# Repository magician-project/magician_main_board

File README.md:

# Magician Main Board for Sensing Robot

This project implements a **multi-laser distance sensing and light control system** on an **Arduino Nano (ATmega328P)**. 

> This README documents the original [`src/kicad/v1`](src/kicad/v1/README.md) board and its Arduino Nano firmware. The current hardware revision is **MagicianCam4** ([`src/kicad/v4`](src/kicad/v4/README.md)), built around a Raspberry Pi Pico 2 with a VL53L5CX multizone ToF sensor; its firmware lives in [`src/pico2`](src/pico2/).

The software that drives this PCB (along with the Camera/ATI/Teensy) is the [Magician Grabber](https://github.com/magician-project/magician_grabber)

It integrates:

- **3x VL53L0X time-of-flight distance sensors** (over I²C, with unique addresses via XSHUT control) 
- **Up to 8 lights** controlled via direct GPIO or a **74HC595 shift register**
- **Extendable up to 64 lights** by daisy chaining more **74HC595 shift registers**
- **Ethernet W5100 support** (Telnet-style interface) 
- **Two analog input buttons** for manual interaction
- **Serial + Ethernet reporting** of sensor readings, light state, and button presses

The firmware cycles lights automatically, can react to distance sensor readings, and supports both **serial commands** and **Ethernet control**.

---

## Features

- 🔦 **3x VL53L0X** laser distance sensors on a shared I²C bus
- 💡 **6x-8x LED light outputs** (6x direct pin mode or 8x via 74HC595 shift register)
- 🌐 **Ethernet W5100 support** with telnet-style server on port `23`
- 🎛️ **Two analog buttons** (for annotations / input)
- ⚡ **Low-level SRAM monitoring** and reset recovery functions
- 🛠️ **Configurable light modes:**
  - Sequential cycling
  - Pulse mode
  - Sensor-based closest-light decision
  - Timed flashing

---

## Setup

Important: Before connecting the board, [read the following guide](doc/connectors.md)!

## Hardware Components

- **Arduino Nano with USB-Micro port/ UNO (ATmega328P)**  
- **VL53L0X distance sensors** (x3)  
- **W5100 Ethernet module/shield**  
- **74HC595 shift register** (optional, for light control)  
- **6 LEDs or lights** (controlled by direct pins or shift register)  
- **2 push buttons** (wired to analog inputs `A6` and `A7`)  

### Pin Mapping

| Component                  | Pin(s) Used         | Notes |
|-----------------------------|---------------------|-------|
| I²C (VL53L0X)              | A4 (SDA), A5 (SCL) | Shared bus |
| VL53L0X XSHUT (x3)         | A0, A1, A2         | Controls sensor reset & addressing |
| Ethernet Reset             | D9                 | Shared with `I2C_EXTRA_PIN` |
| Direct Light Outputs       | D3, D4, D5, D6, D7, D8 | Default pin mode |
| 74HC595 Latch (STCP)       | D3                 | Used if shift register enabled |
| 74HC595 Clock (SHCP)       | D4                 | 〃 |
| 74HC595 Data (DS)          | D5                 | 〃 |
| 74HC595 OE (Enable)        | D2                 | Active low |
| 74HC595 SRCLR (Clear)      | A3                 | Active low |
| Buttons                    | A6, A7             | Analog threshold detection |

---

## Software Setup

1. **Clone this repository** and the Pololu VL53L0X Arduino library:
   ```bash
   git clone https://github.com/YOUR_GITHUB_USERNAME/arduino-nano-vl53l0x-ethernet
   cd arduino-nano-vl53l0x-ethernet
   git clone https://github.com/pololu/vl53l0x-arduino
   cp vl53l0x-arduino/VL53L0X.cpp ./
   cp vl53l0x-arduino/VL53L0X.h ./

    Fix Arduino Nano memory constraints (important!):
    The VL53L0X library is heavy and may cause stack overflow resets.
    To prevent this, reduce the serial buffer sizes:

    Edit:

~/.arduino15/packages/arduino/hardware/avr/1.8.6/cores/arduino/HardwareSerial.h

Change:

    #define SERIAL_TX_BUFFER_SIZE 16
    #define SERIAL_RX_BUFFER_SIZE 8

    With this, the sketch fits:

        Program storage: ~66% used

        Dynamic memory: ~80% used (401 bytes free)

    Install dependencies in Arduino IDE:

        Wire.h (I²C, built-in)

        SPI.h (Ethernet, built-in)

        Ethernet.h (W5100)

    Upload the sketch to your Arduino Nano.

Serial & Ethernet Commands

To connect to Ethernet (assuming you are on the correct subnet)
```
telnet 192.168.137.64
```

To connect using USB/Serial (assuming you are connected over USB)
```
sudo apt install picocom
picocom -b 115200 /dev/ttyUSB0  --imap lfcrlf 
Ctrl + A + Q to exit
```

When connected via USB serial or Ethernet Telnet (port 23), you can control and query the system by supplying the following command bytes.

Command	Description:

| Command                     | Dangerous           | Description |
|-----------------------------|---------------------|-------|
| v              | No    | Print firmware version |
| h              | Yes   | Enable 74HC595 mode + auto light cycling |
| i              | Yes   | Disable 74HC595 (direct pin mode) |
| o              | Maybe | Continuous lights (disable pulsing) |
| p              | Maybe | Switch to pulsing of 500μs / Subsequent calls increase pulse length by 500µs |
| r              | No    | Reset light cycling |
| a              | No    | Enable sensor-based light selection |
| t              | No    | Enable custom cycling mode (mode 3) |
| y              | No    | Flash lights for 10s, then turn off |
| z              | No    | Turn off all lights and reset Arduino |
| 0-6            | Yes   | Manually activate light with number #N |
| +              | Yes   | Step to next light |
| f              | No    | Disable serial/Ethernet reporting |
| x              | No    | (Ethernet only) Print local IP + hardware status | 
| b              | No    | Make Analog Buttons have binary output  1/0 | 
| n              | No    | Make Analog Buttons have non-binary output  0-1024 | 

Commands marked as potentially dangerous directly alter light states that can be dangerous when
using a connected Camera Board that over volts lights. Please see [the setup guide](doc/connectors.md) to understand why. 

Data Reporting

When enabled, the Arduino periodically outputs status lines in CSV format:

<time_ms>,<button1>,<button2>,<distance1>,<distance2>,<distance3>,<light1>,<light2>,...<light6>

Example:

1050,0,1,523,812,1500,1,0,0,0,0,0

    time_ms – system uptime in ms

    button1/button2 – 0 or 1

    distanceN – measured distance in mm (F = failed, H = too high, 0 = inactive)

    lightN – 1 if active, 0 otherwise

Memory & Stability Notes

    Free SRAM is checked at startup; if less than 231 bytes are available, instability is expected.

    Use the reduced VL53L0X library and shrunk serial buffers for stability.

    A resetFunc() software reset is available to recover from low memory conditions.

Versioning

    Version: 0.26

    Major/minor defined in VERSION_MAJOR, VERSION_MINOR.

License

MIT License.
This project uses Pololu’s VL53L0X Arduino Library

Possible Future Improvements

    Add MQTT over Ethernet for IoT integration

    Support ESP32 (more SRAM, WiFi support, no buffer hacks needed)

    Add dynamic light patterns and user-configurable modes

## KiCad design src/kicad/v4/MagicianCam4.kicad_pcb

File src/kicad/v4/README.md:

Designed by Giulio Vivo

# MagicianCam4

Current revision of the Magician camera/sensing board, built around a **Raspberry Pi Pico 2 (RP2350)** instead of the Arduino Nano used in [`v1/`](../v1/README.md). Firmware lives in [`src/pico2/`](../../pico2/).

Main changes over v1:

- **VL53L5CX multizone ToF sensor** (8x8 = 64 distance zones) replacing the 3x VL53L0X single-zone sensors.
- **MCP23018 I²C I/O expander** for buttons and light control, replacing the 74HC595 shift register chain.
- Exposure-synced LED strobing with per-COB thermal budgeting, since the LED COBs are driven above their rated voltage and rely on strict pulse-width/duty-cycle limits to survive.
- Ethernet connectivity kept compatible with the camera board.

See the MAGICIAN D3.3 deliverable for the background on the sensor/board redesign (split Main + LED-strobe + Ethernet board layout, move from Arduino Mega/Nano to a smaller microcontroller footprint).

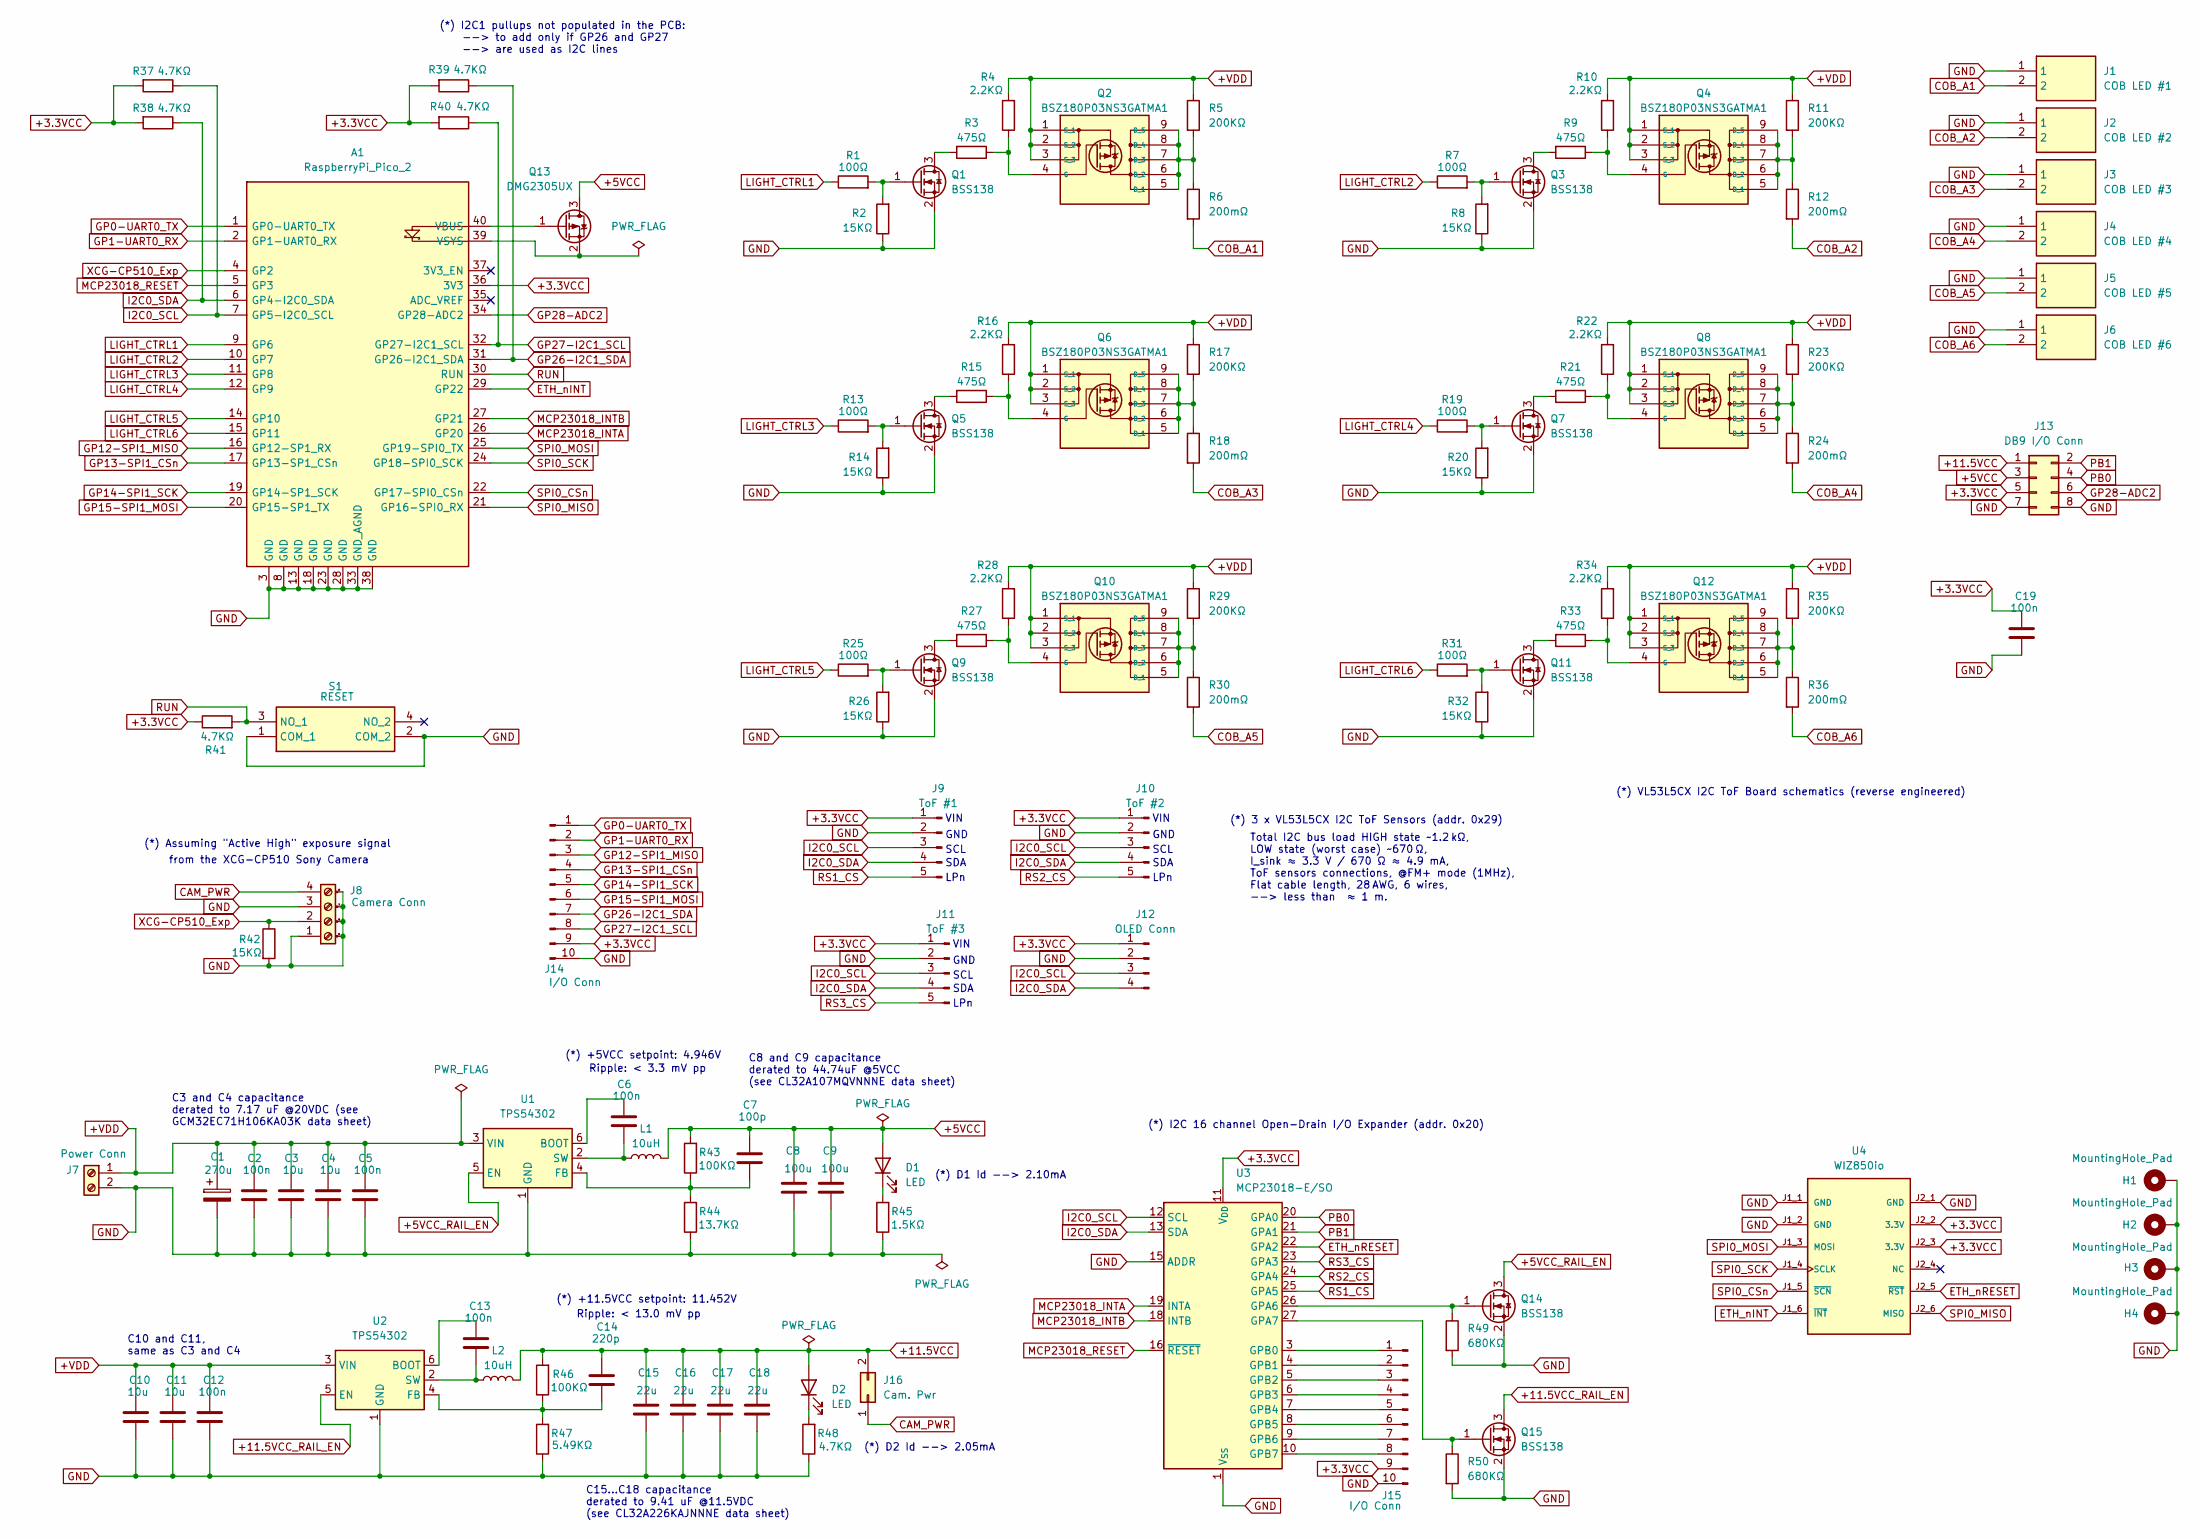
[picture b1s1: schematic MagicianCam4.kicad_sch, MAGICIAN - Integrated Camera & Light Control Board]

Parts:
A1: RaspberryPi_Pico_2; RaspberryPi_Pico_THT
C1: 270u; EEHZS1H221P
C2, C5, C12, C19: 100n; C_0603_1608Metric_HANDSOLD
C3, C4, C10, C11: 10u; GCM32EC71H106KA03K
C6, C13: 100n; C_0805_2012Metric__HANDSOLD
C7: 100p; C_0603_1608Metric_HANDSOLD
C8, C9: 100u; CL32A107MQVNNNE
C14: 220p; C_0603_1608Metric_HANDSOLD
C15, C16, C17, C18: 22u; CL32A226KAJNNNE
D1, D2: LED; LSQ97601N1Q21
H1, H2, H3, H4: MountingHole_Pad; MountingHole_2.2mm_M2_DIN965_Pad
J1: COB LED #1; 640456-2; Manufacturer_Part_Number 640456-2
J2: COB LED #2; 640456-2; Manufacturer_Part_Number 640456-2
J3: COB LED #3; 640456-2; Manufacturer_Part_Number 640456-2
J4: COB LED #4; 640456-2; Manufacturer_Part_Number 640456-2
J5: COB LED #5; 640456-2; Manufacturer_Part_Number 640456-2
J6: COB LED #6; 640456-2; Manufacturer_Part_Number 640456-2
J7: Power Conn; TC0203620000G
J8: Camera Conn; RS 790-1102
J9: ToF #1; PinHeader_1x05_P2.54mm_Vertical
J10: ToF #2; PinHeader_1x05_P2.54mm_Vertical
J11: ToF #3; PinHeader_1x05_P2.54mm_Vertical
J12: OLED Conn; PinHeader_1x04_P2.54mm_Vertical
J13: DB9 I/O Conn; T821108A1S100CEU
J14, J15: I/O Conn; PinHeader_1x10_P2.54mm_Vertical
J16: Cam. Pwr; PinHeader_1x02_P2.54mm_Vertical
L1, L2: 10uH; SLF10165
Q1, Q3, Q5, Q7, Q9, Q11, Q14, Q15: BSS138; SOT-23_HANDSOLD2
Q2, Q4, Q6, Q8, Q10, Q12: BSZ180P03NS3GATMA1
Q13: DMG2305UX; SOT-23_HANDSOLD2
R1, R7, R13, R19, R25, R31: 100Ω; R_0603_1608Metric_HANDSOLD
R2, R8, R14, R20, R26, R32, R42: 15KΩ; R_0603_1608Metric_HANDSOLD
R3, R9, R15, R21, R27, R33: 475Ω; R_0805_2012Metric_Pad1.20x1.40mm_HandSolder
R4, R10, R16, R22, R28, R34: 2.2KΩ; R_1206_3216Metric_Pad1.30x1.75mm_HandSolder
R5, R11, R17, R23, R29, R35: 200KΩ; R_0603_1608Metric_HANDSOLD
R6, R12, R18, R24, R30, R36: 200mΩ; R_2512_6332Metric_Pad1.40x3.35mm_HandSolder
R37, R38, R48: 4.7KΩ; R_0603_1608Metric_HANDSOLD
R39, R40, R41: 4.7KΩ; R_0603_1608Metric
R43, R46: 100KΩ; R_0603_1608Metric_HANDSOLD
R44: 13.7KΩ; R_0603_1608Metric_HANDSOLD
R45: 1.5KΩ; R_0603_1608Metric_HANDSOLD
R47: 5.49KΩ; R_0603_1608Metric_HANDSOLD
R49, R50: 680KΩ; R_0603_1608Metric_HANDSOLD
S1: RESET; PTS641SM25SMTR2LFS; Manufacturer_Part_Number PTS641 SM25 SMTR2 LFS
U1, U2: TPS54302; SOT-23-THIN-6_HANDSOLD
U3: MCP23018-E/SO; SOIC-28W_7.5x17.9mm_P1.27mm
U4: WIZ850io; WIZ850IO; PARTREV V1.0

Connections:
+3.3VCC: A1.36 (3V3), C19.1, J9.1, J10.1, J11.1, J12.1, J13.5, J14.9, J15.9, R37.2, R38.2, R39.2, R40.2, R41.1, U3.11 (V_{DD}), U4.J2_2 (3.3V), U4.J2_3 (3.3V)
+5VCC: C7.1, C8.1, C9.1, D1.2 (A), J13.3, L1.2, Q13.3 (D), R43.2
+5VCC_RAIL_EN: Q14.3 (D), U1.5 (EN)
+11.5VCC: C14.1, C15.1, C16.1, C17.1, C18.1, D2.2 (A), J13.1, J16.2, L2.2, R46.2
+11.5VCC_RAIL_EN: Q15.3 (D), U2.5 (EN)
+VDD: C1.1, C2.1, C3.1, C4.1, C5.1, C10.1, C11.1, C12.1, J7.1, Q2.1 (S_1), Q2.2 (S_2), Q2.3 (S_3), Q4.1 (S_1), Q4.2 (S_2), Q4.3 (S_3), Q6.1 (S_1), Q6.2 (S_2), Q6.3 (S_3), Q8.1 (S_1), Q8.2 (S_2), Q8.3 (S_3), Q10.1 (S_1), Q10.2 (S_2), Q10.3 (S_3), Q12.1 (S_1), Q12.2 (S_2), Q12.3 (S_3), R4.2, R5.1, R10.2, R11.1, R16.2, R17.1, R22.2, R23.1, R28.2, R29.1, R34.2, R35.1, U1.3 (VIN), U2.3 (VIN)
CAM_PWR: J8.4, J16.1
COB_A1: J1.2, R6.2
COB_A2: J2.2, R12.2
COB_A3: J3.2, R18.2
COB_A4: J4.2, R24.2
COB_A5: J5.2, R30.2
COB_A6: J6.2, R36.2
ETH_nINT: A1.29 (GP22), U4.J1_6 (~INT)
ETH_nRESET: U3.22 (GPA2), U4.J2_5 (~RST)
GND: A1.3 (GND), A1.8 (GND), A1.13 (GND), A1.18 (GND), A1.23 (GND), A1.28 (GND), A1.33 (GND_AGND), A1.38 (GND), C1.2, C2.2, C3.2, C4.2, C5.2, C8.2, C9.2, C10.2, C11.2, C12.2, C15.2, C16.2, C17.2, C18.2, C19.2, H1.1 (1_1), H2.1 (1_1), H3.1 (1_1), H4.1 (1_1), J1.1, J2.1, J3.1, J4.1, J5.1, J6.1, J7.2, J8.1, J8.3, J8.5 (Pin_1), J8.6 (Pin_1), J8.7 (Pin_1), J8.8 (Pin_1), J9.2, J10.2, J11.2, J12.2, J13.7, J13.8, J14.10, J15.10, Q1.2 (S), Q3.2 (S), Q5.2 (S), Q7.2 (S), Q9.2 (S), Q11.2 (S), Q14.2 (S), Q15.2 (S), R2.1, R8.1, R14.1, R20.1, R26.1, R32.1, R42.2, R44.1, R45.1, R47.1, R48.1, R49.2, R50.2, S1.1 (COM_1), S1.2 (COM_2), U1.1 (GND), U2.1 (GND), U3.1 (V_{SS}), U3.15 (ADDR), U4.J1_1 (GND), U4.J1_2 (GND), U4.J2_1 (GND)
GP0-UART0_TX: A1.1 (GP0-UART0_TX), J14.1
GP1-UART0_RX: A1.2 (GP1-UART0_RX), J14.2
GP12-SPI1_MISO: A1.16 (GP12-SP1_RX), J14.3
GP13-SPI1_CSn: A1.17 (GP13-SP1_CSn), J14.4
GP14-SPI1_SCK: A1.19 (GP14-SP1_SCK), J14.5
GP15-SPI1_MOSI: A1.20 (GP15-SP1_TX), J14.6
GP26-I2C1_SDA: A1.31 (GP26-I2C1_SDA), J14.7, R39.1
GP27-I2C1_SCL: A1.32 (GP27-I2C1_SCL), J14.8, R40.1
GP28-ADC2: A1.34 (GP28-ADC2), J13.6
I2C0_SCL: A1.7 (GP5-I2C0_SCL), J9.3, J10.3, J11.3, J12.3, R37.1, U3.12 (SCL)
I2C0_SDA: A1.6 (GP4-I2C0_SDA), J9.4, J10.4, J11.4, J12.4, R38.1, U3.13 (SDA)
LIGHT_CTRL1: A1.9 (GP6), R1.1
LIGHT_CTRL2: A1.10 (GP7), R7.1
LIGHT_CTRL3: A1.11 (GP8), R13.1
LIGHT_CTRL4: A1.12 (GP9), R19.1
LIGHT_CTRL5: A1.14 (GP10), R25.1
LIGHT_CTRL6: A1.15 (GP11), R31.1
MCP23018_INTA: A1.26 (GP20), U3.19 (INTA)
MCP23018_INTB: A1.27 (GP21), U3.18 (INTB)
MCP23018_RESET: A1.5 (GP3), U3.16 (~RESET)
unnamed: A1.40 (VBUS), Q13.1 (G)
unnamed: A1.39 (VSYS), Q13.2 (S)
unnamed: D1.1 (K), R45.2
unnamed: D2.1 (K), R48.2
unnamed: J15.1, U3.3 (GPB0)
unnamed: J15.2, U3.4 (GPB1)
unnamed: J15.3, U3.5 (GPB2)
unnamed: J15.4, U3.6 (GPB3)
unnamed: J15.5, U3.7 (GPB4)
unnamed: J15.6, U3.8 (GPB5)
unnamed: J15.7, U3.9 (GPB6)
unnamed: J15.8, U3.10 (GPB7)
unnamed: Q1.3 (D), R3.2
unnamed: Q1.1 (G), R1.2, R2.2
unnamed: Q2.5 (D_1), Q2.6 (D_2), Q2.7 (D_3), Q2.8 (D_4), Q2.9 (D_5), R5.2, R6.1
unnamed: Q2.4 (G), R3.1, R4.1
unnamed: Q3.3 (D), R9.2
unnamed: Q3.1 (G), R7.2, R8.2
unnamed: Q4.5 (D_1), Q4.6 (D_2), Q4.7 (D_3), Q4.8 (D_4), Q4.9 (D_5), R11.2, R12.1
unnamed: Q4.4 (G), R9.1, R10.1
unnamed: Q5.3 (D), R15.2
unnamed: Q5.1 (G), R13.2, R14.2
unnamed: Q6.5 (D_1), Q6.6 (D_2), Q6.7 (D_3), Q6.8 (D_4), Q6.9 (D_5), R17.2, R18.1
unnamed: Q6.4 (G), R15.1, R16.1
unnamed: Q7.3 (D), R21.2
unnamed: Q7.1 (G), R19.2, R20.2
unnamed: Q8.5 (D_1), Q8.6 (D_2), Q8.7 (D_3), Q8.8 (D_4), Q8.9 (D_5), R23.2, R24.1
unnamed: Q8.4 (G), R21.1, R22.1
unnamed: Q9.3 (D), R27.2
unnamed: Q9.1 (G), R25.2, R26.2
unnamed: Q10.5 (D_1), Q10.6 (D_2), Q10.7 (D_3), Q10.8 (D_4), Q10.9 (D_5), R29.2, R30.1
unnamed: Q10.4 (G), R27.1, R28.1
unnamed: Q11.3 (D), R33.2
unnamed: Q11.1 (G), R31.2, R32.2
unnamed: Q12.5 (D_1), Q12.6 (D_2), Q12.7 (D_3), Q12.8 (D_4), Q12.9 (D_5), R35.2, R36.1
unnamed: Q12.4 (G), R33.1, R34.1
unnamed: Q14.1 (G), R49.1, U3.26 (GPA6)
unnamed: Q15.1 (G), R50.1, U3.27 (GPA7)
unnamed: C6.1, U1.6 (BOOT)
unnamed: C7.2, R43.1, R44.2, U1.4 (FB)
unnamed: C6.2, L1.1, U1.2 (SW)
unnamed: C13.1, U2.6 (BOOT)
unnamed: C14.2, R46.1, R47.2, U2.4 (FB)
unnamed: C13.2, L2.1, U2.2 (SW)
PB0: J13.4, U3.20 (GPA0)
PB1: J13.2, U3.21 (GPA1)
RS1_CS: J9.5, U3.25 (GPA5)
RS2_CS: J10.5, U3.24 (GPA4)
RS3_CS: J11.5, U3.23 (GPA3)
RUN: A1.30 (RUN), R41.2, S1.3 (NO_1)
SPI0_CSn: A1.22 (GP17-SPI0_CSn), U4.J1_5 (~SCN)
SPI0_MISO: A1.21 (GP16-SPI0_RX), U4.J2_6 (MISO)
SPI0_MOSI: A1.25 (GP19-SPI0_TX), U4.J1_3 (MOSI)
SPI0_SCK: A1.24 (GP18-SPI0_SCK), U4.J1_4 (SCLK)
XCG-CP510_Exp: A1.4 (GP2), J8.2, R42.1

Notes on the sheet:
from the XCG-CP510 Sony Camera
LPn
Ripple: < 13.0 mV pp
(*) +5VCC setpoint: 4.946V
(*) I2C 16 channel Open-Drain I/O Expander (addr. 0x20)
C3 and C4 capacitance derated to 7.17 uF @20VDC (see GCM32EC71H106KA03K data sheet)
Total I2C bus load HIGH state ~1.2 kΩ, LOW state (worst case) ~670 Ω, I_sink ≈ 3.3 V / 670 Ω ≈ 4.9 mA, ToF sensors connections, @FM+ mode (1MHz), Flat cable length, 28 AWG, 6 wires, --> less than ≈ 1 m.
VIN
GND
SDA
C8 and C9 capacitance derated to 44.74uF @5VCC (see CL32A107MQVNNNE data sheet)
SCL
C15...C18 capacitance derated to 9.41 uF @11.5VDC (see CL32A226KAJNNNE data sheet)
(*) D2 Id --> 2.05mA
C10 and C11, same as C3 and C4
(*) D1 Id --> 2.10mA
(*) VL53L5CX I2C ToF Board schematics (reverse engineered)
(*) Assuming "Active High" exposure signal
Ripple: < 3.3 mV pp
(*) 3 x VL53L5CX I2C ToF Sensors (addr. 0x29)
(*) I2C1 pullups not populated in the PCB: --> to add only if GP26 and GP27 --> are used as I2C lines
(*) +11.5VCC setpoint: 11.452V

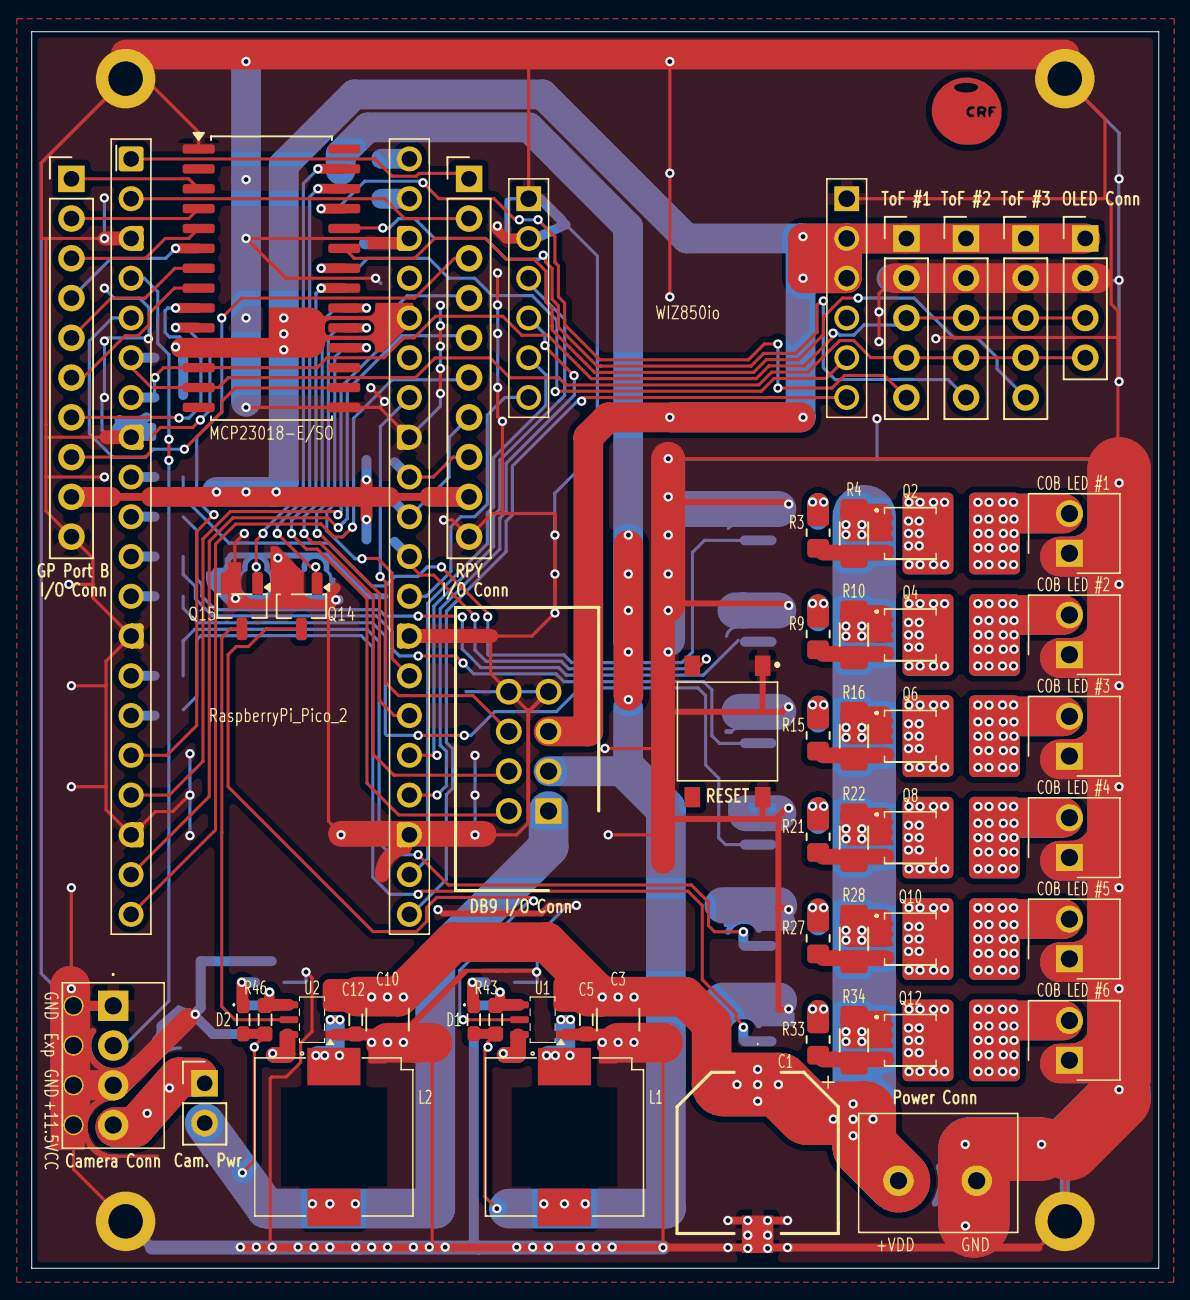
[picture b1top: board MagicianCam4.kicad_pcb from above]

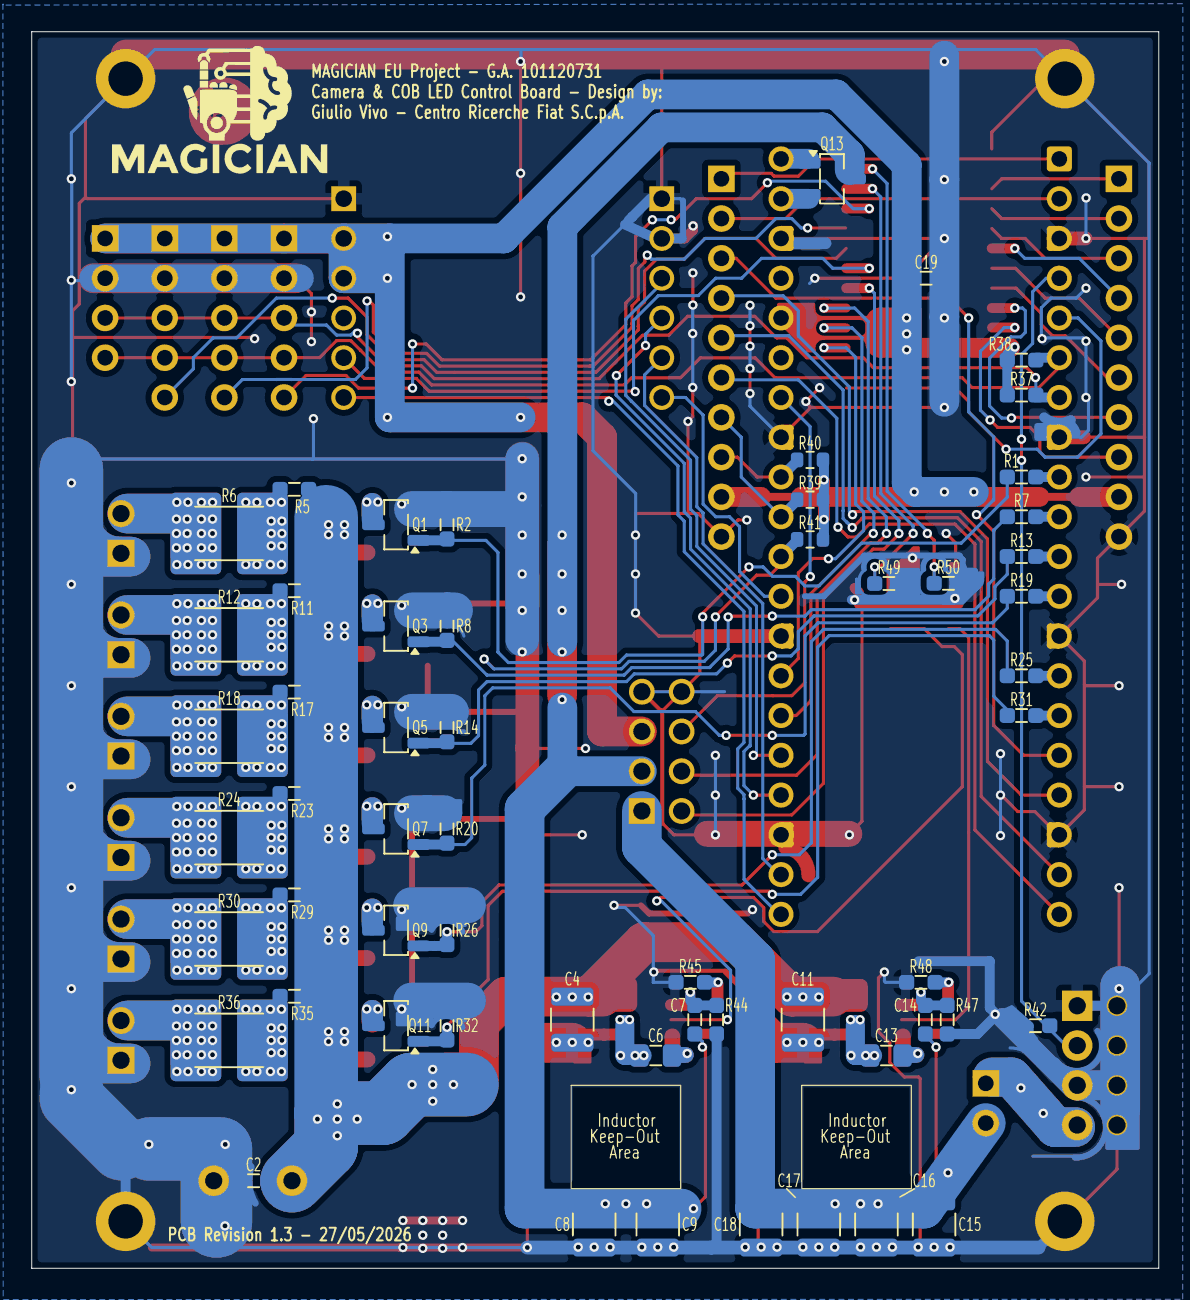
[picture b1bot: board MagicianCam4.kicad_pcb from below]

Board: 2 copper layers, 72.0 x 79.0 mm, 114 parts (57 on the bottom side), 91 nets.

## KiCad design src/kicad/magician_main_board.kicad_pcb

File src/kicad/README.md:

# KiCad Boards

This directory holds the KiCad projects for the Magician sensing PCBs, organized by hardware revision:

- [`v1/`](v1/README.md) — the original Magician Main Board (Arduino Nano, 3x VL53L0X, 74HC595 shift register). Superseded, kept for reference.
- [`v4/`](v4/README.md) — **MagicianCam4**, the current board (Raspberry Pi Pico 2, VL53L5CX multizone ToF sensor, MCP23018 I/O expander).

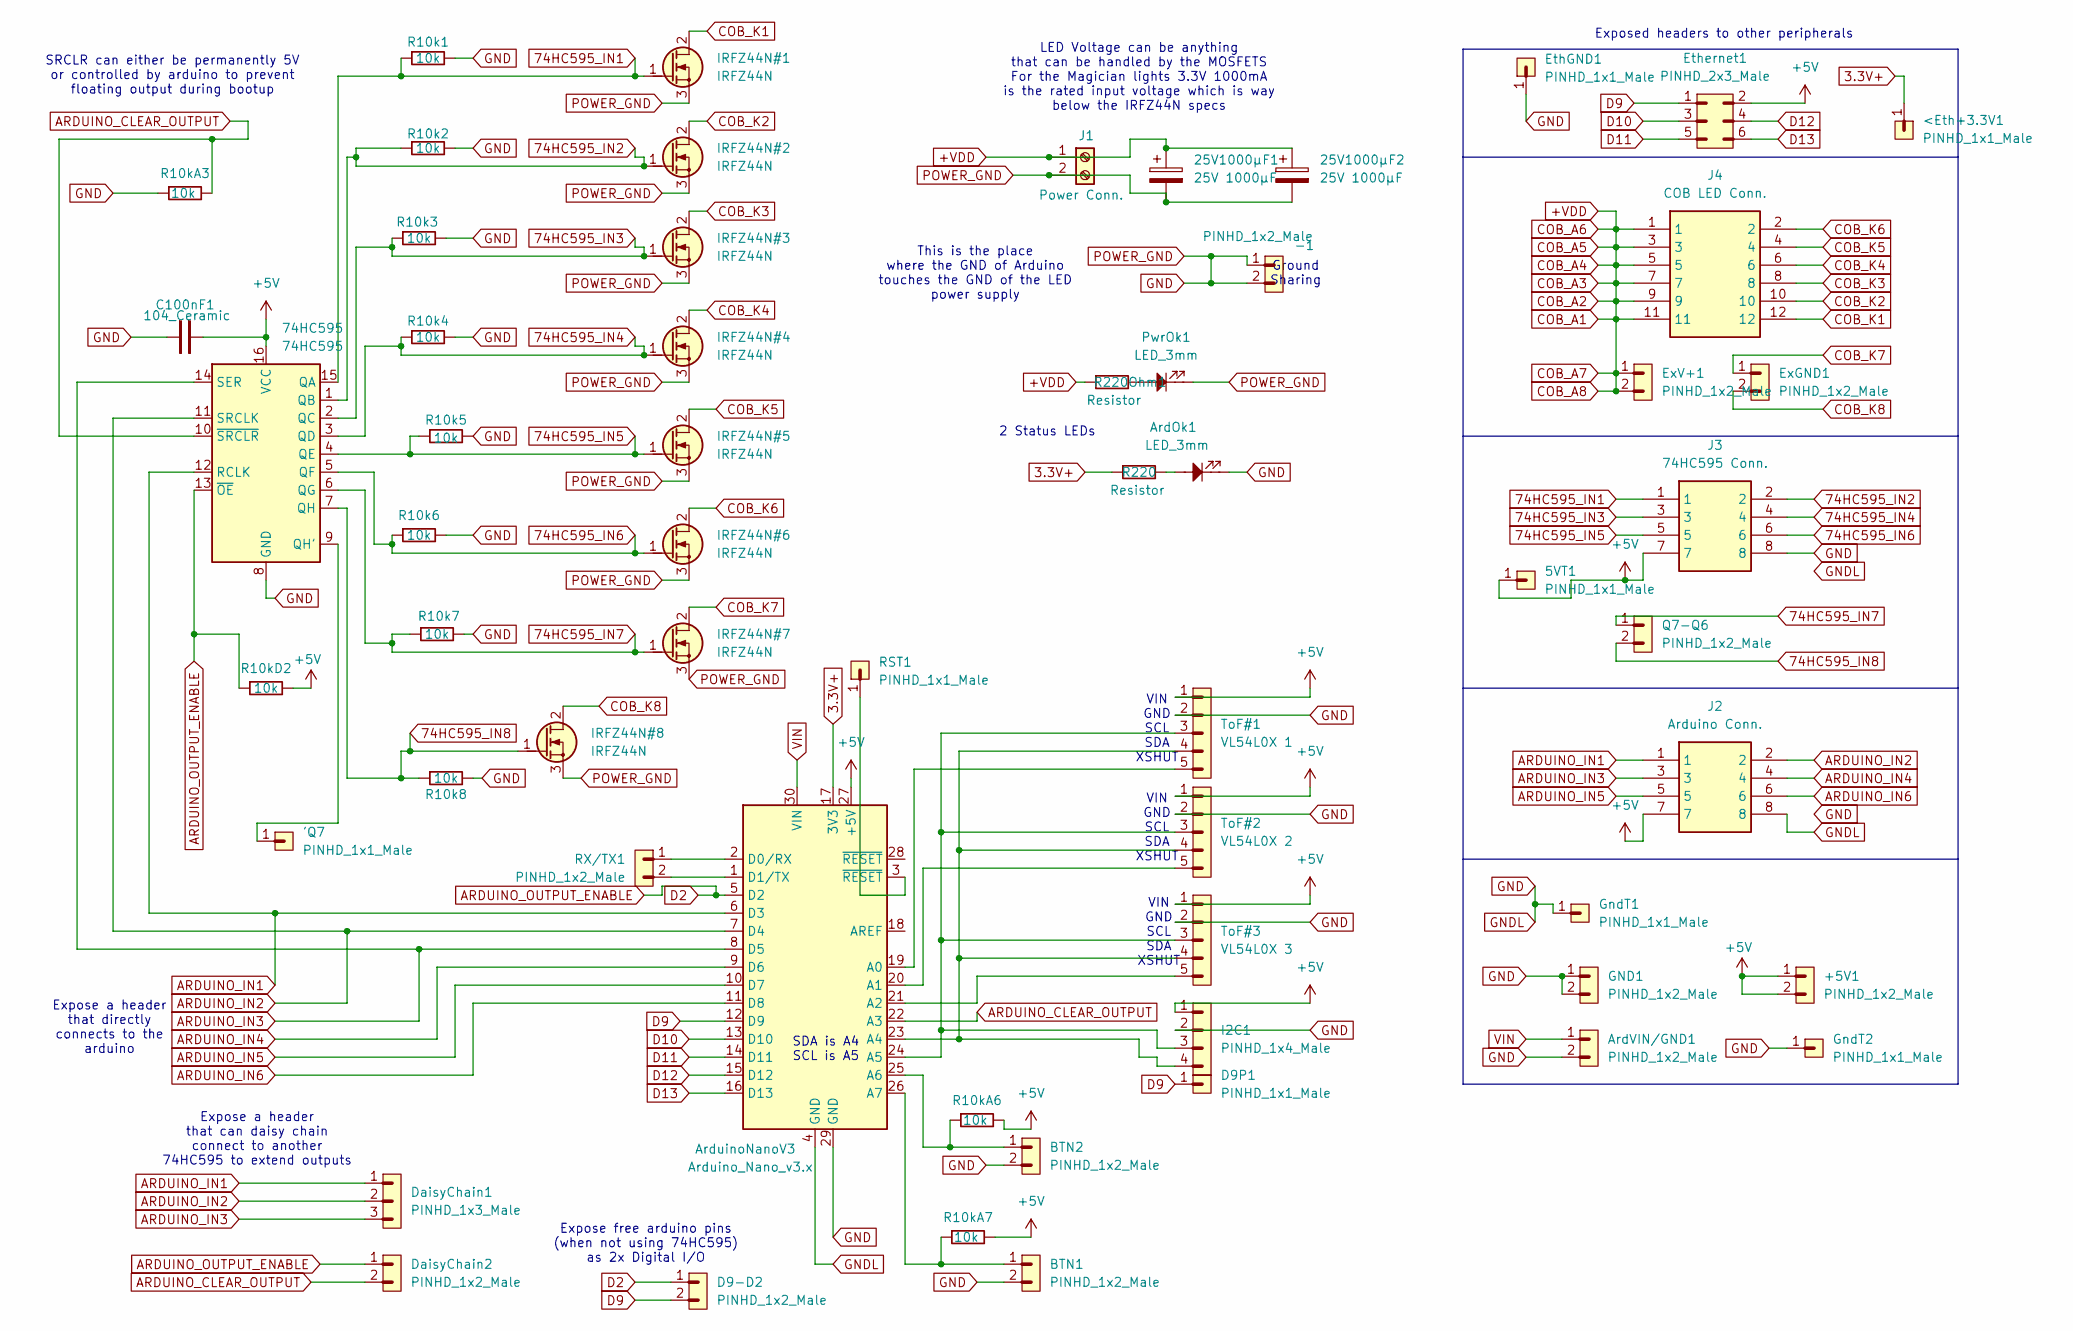
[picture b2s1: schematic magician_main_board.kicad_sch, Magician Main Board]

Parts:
5VT1: PINHD_1x1_Male; PinHeader_1x01_P2.54mm_Vertical
25V1000μF1, 25V1000μF2: 25V 1000μF; C_Radial_D6.3mm_H11.0mm_P2.50mm
74HC595: 74HC595; DIP-16_W7.62mm_Socket
'Q7: PINHD_1x1_Male; PinHeader_1x01_P2.54mm_Vertical
+5V1: PINHD_1x2_Male; PinHeader_1x02_P2.54mm_Vertical
-1: PINHD_1x2_Male; PinHeader_1x02_P2.54mm_Vertical
<Eth+3.3V1: PINHD_1x1_Male; PinHeader_1x01_P2.54mm_Vertical
ArdOk1: LED_3mm; LED_D3.0mm
ArdVIN/GND1: PINHD_1x2_Male; PinHeader_1x02_P2.54mm_Vertical
ArduinoNanoV3: Arduino_Nano_v3.x; Arduino_Nano
BTN1, BTN2: PINHD_1x2_Male; PinHeader_1x02_P2.54mm_Vertical
C100nF1: 104_Ceramic; C_Disc_D5.0mm_W2.5mm_P2.50mm
D9-D2: PINHD_1x2_Male; PinHeader_1x02_P2.54mm_Vertical
D9P1: PINHD_1x1_Male; PinHeader_1x01_P2.54mm_Vertical
DaisyChain1: PINHD_1x3_Male; PinHeader_1x03_P2.54mm_Vertical
DaisyChain2: PINHD_1x2_Male; PinHeader_1x02_P2.54mm_Vertical
EthGND1: PINHD_1x1_Male; PinHeader_1x01_P2.54mm_Vertical
Ethernet1: PINHD_2x3_Male; PinHeader_2x03_P2.54mm_Vertical
ExGND1: PINHD_1x2_Male; PinHeader_1x02_P2.54mm_Vertical
ExV+1: PINHD_1x2_Male; PinHeader_1x02_P2.54mm_Vertical
GND1: PINHD_1x2_Male; PinHeader_1x02_P2.54mm_Vertical
GndT1, GndT2: PINHD_1x1_Male; PinHeader_1x01_P2.54mm_Vertical
I2C1: PINHD_1x4_Male; PinHeader_1x04_P2.54mm_Vertical
IRFZ44N#1, IRFZ44N#2, IRFZ44N#3, IRFZ44N#4, IRFZ44N#5, IRFZ44N#6, IRFZ44N#7, IRFZ44N#8: IRFZ44N; TO-220-3_Vertical_GDS
J1: Power Conn.; 691210910002
J2: Arduino Conn.; T821108A1S100CEU; Manufacturer_Part_Number T821108A1S100CEU; Mouser Part Number N/A
J3: 74HC595 Conn.; T821108A1S100CEU; Manufacturer_Part_Number T821108A1S100CEU; Mouser Part Number N/A
J4: COB LED Conn.; T821112A1S100CEU; Manufacturer_Part_Number T821112A1S100CEU; Mouser Part Number N/A
PwrOk1: LED_3mm; LED_D3.0mm
Q7-Q6: PINHD_1x2_Male; PinHeader_1x02_P2.54mm_Vertical
R10k1, R10k2, R10k3, R10k4, R10k5, R10k6, R10k7, R10k8, R10kA3, R10kA6, R10kA7, R10kD2: 10k; R_Axial_DIN0207_L6.3mm_D2.5mm_P10.16mm_Horizontal
R220, R220Ohm1: Resistor; R_Axial_DIN0207_L6.3mm_D2.5mm_P10.16mm_Horizontal
RST1: PINHD_1x1_Male; PinHeader_1x01_P2.54mm_Vertical
RX/TX1: PINHD_1x2_Male; PinHeader_1x02_P2.54mm_Vertical
ToF#1: VL54L0X 1; PinHeader_1x05_P2.54mm_Vertical
ToF#2: VL54L0X 2; PinHeader_1x05_P2.54mm_Vertical
ToF#3: VL54L0X 3; PinHeader_1x05_P2.54mm_Vertical

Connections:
3.3V+: <Eth+3.3V1.1, ArduinoNanoV3.17 (3V3), R220.1
74HC595_IN1: 74HC595.15 (QA), IRFZ44N#1.1 (G), J3.1, R10k1.1
74HC595_IN2: 74HC595.1 (QB), IRFZ44N#2.1 (G), J3.2, R10k2.1
74HC595_IN3: 74HC595.2 (QC), IRFZ44N#3.1 (G), J3.3, R10k3.1
74HC595_IN4: 74HC595.3 (QD), IRFZ44N#4.1 (G), J3.4, R10k4.1
74HC595_IN5: 74HC595.4 (QE), IRFZ44N#5.1 (G), J3.5, R10k5.1
74HC595_IN6: 74HC595.5 (QF), IRFZ44N#6.1 (G), J3.6, R10k6.1
74HC595_IN7: 74HC595.6 (QG), IRFZ44N#7.1 (G), Q7-Q6.1, R10k7.1
74HC595_IN8: 74HC595.7 (QH), IRFZ44N#8.1 (G), Q7-Q6.2, R10k8.1
+5V: 5VT1.1, 74HC595.16 (VCC), +5V1.1, +5V1.2, ArduinoNanoV3.27 (+5V), C100nF1.2, Ethernet1.2, I2C1.1, J2.7, J3.7, R10kA6.2, R10kA7.2, R10kD2.2, ToF#1.1, ToF#2.1, ToF#3.1
+VDD: 25V1000μF1.1, 25V1000μF2.1, ExV+1.1, ExV+1.2, J1.1, J4.1, J4.3, J4.5, J4.7, J4.9, J4.11, R220Ohm1.1
ARDUINO_CLEAR_OUTPUT: 74HC595.10 (~SRCLR), ArduinoNanoV3.22 (A3), DaisyChain2.2, R10kA3.2
ARDUINO_IN1: 74HC595.12 (RCLK), ArduinoNanoV3.6 (D3), DaisyChain1.1, J2.1
ARDUINO_IN2: 74HC595.11 (SRCLK), ArduinoNanoV3.7 (D4), DaisyChain1.2, J2.2
ARDUINO_IN3: 74HC595.14 (SER), ArduinoNanoV3.8 (D5), DaisyChain1.3, J2.3
ARDUINO_IN4: ArduinoNanoV3.9 (D6), J2.4
ARDUINO_IN5: ArduinoNanoV3.10 (D7), J2.5
ARDUINO_IN6: ArduinoNanoV3.11 (D8), J2.6
ARDUINO_OUTPUT_ENABLE: 74HC595.13 (~OE), ArduinoNanoV3.5 (D2), D9-D2.1, DaisyChain2.1, R10kD2.1
COB_K1: IRFZ44N#1.2 (D), J4.12
COB_K2: IRFZ44N#2.2 (D), J4.10
COB_K3: IRFZ44N#3.2 (D), J4.8
COB_K4: IRFZ44N#4.2 (D), J4.6
COB_K5: IRFZ44N#5.2 (D), J4.4
COB_K6: IRFZ44N#6.2 (D), J4.2
COB_K7: ExGND1.1, IRFZ44N#7.2 (D)
COB_K8: ExGND1.2, IRFZ44N#8.2 (D)
D9: ArduinoNanoV3.12 (D9), D9-D2.2, D9P1.1, Ethernet1.1
D10: ArduinoNanoV3.13 (D10), Ethernet1.3
D11: ArduinoNanoV3.14 (D11), Ethernet1.5
D12: ArduinoNanoV3.15 (D12), Ethernet1.4
D13: ArduinoNanoV3.16 (D13), Ethernet1.6
GND: 25V1000μF1.2, 25V1000μF2.2, 74HC595.8 (GND), -1.1, -1.2, ArdOk1.1, ArdVIN/GND1.2, ArduinoNanoV3.4 (GND), ArduinoNanoV3.29 (GND), BTN1.2, BTN2.2, C100nF1.1, EthGND1.1, GND1.1, GND1.2, GndT1.1, GndT2.1, I2C1.2, IRFZ44N#1.3 (S), IRFZ44N#2.3 (S), IRFZ44N#3.3 (S), IRFZ44N#4.3 (S), IRFZ44N#5.3 (S), IRFZ44N#6.3 (S), IRFZ44N#7.3 (S), IRFZ44N#8.3 (S), J1.2, J2.8, J3.8, PwrOk1.1, R10k1.2, R10k2.2, R10k3.2, R10k4.2, R10k5.2, R10k6.2, R10k7.2, R10k8.2, R10kA3.1, ToF#1.2, ToF#2.2, ToF#3.2
unnamed: 74HC595.9 (QH'), 'Q7.1
unnamed: ArdOk1.2, R220.2
unnamed: ArduinoNanoV3.19 (A0), ToF#1.5
unnamed: ArduinoNanoV3.20 (A1), ToF#2.5
unnamed: ArduinoNanoV3.21 (A2), ToF#3.5
unnamed: ArduinoNanoV3.23 (A4), I2C1.4, ToF#1.4, ToF#2.4, ToF#3.4
unnamed: ArduinoNanoV3.24 (A5), I2C1.3, ToF#1.3, ToF#2.3, ToF#3.3
unnamed: ArduinoNanoV3.25 (A6), BTN2.1, R10kA6.1
unnamed: ArduinoNanoV3.26 (A7), BTN1.1, R10kA7.1
unnamed: ArduinoNanoV3.2 (D0/RX), RX/TX1.1
unnamed: ArduinoNanoV3.1 (D1/TX), RX/TX1.2
unnamed: ArduinoNanoV3.3 (~RESET), RST1.1
unnamed: PwrOk1.2, R220Ohm1.2
VIN: ArdVIN/GND1.1, ArduinoNanoV3.30 (VIN)

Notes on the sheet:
Exposed headers to other peripherals
VIN GND SCL SDA XSHUT
Expose a header that directly connects to the arduino
LED Voltage can be anything that can be handled by the MOSFETS For the Magician lights 3.3V 1000mA is the rated input voltage which is way below the IRFZ44N specs
Expose a header that can daisy chain connect to another 74HC595 to extend outputs
Ground Sharing
Expose free arduino pins (when not using 74HC595) as 2x Digital I/O
2 Status LEDs
SRCLR can either be permanently 5V or controlled by arduino to prevent floating output during bootup
This is the place where the GND of Arduino touches the GND of the LED power supply
SDA is A4 SCL is A5

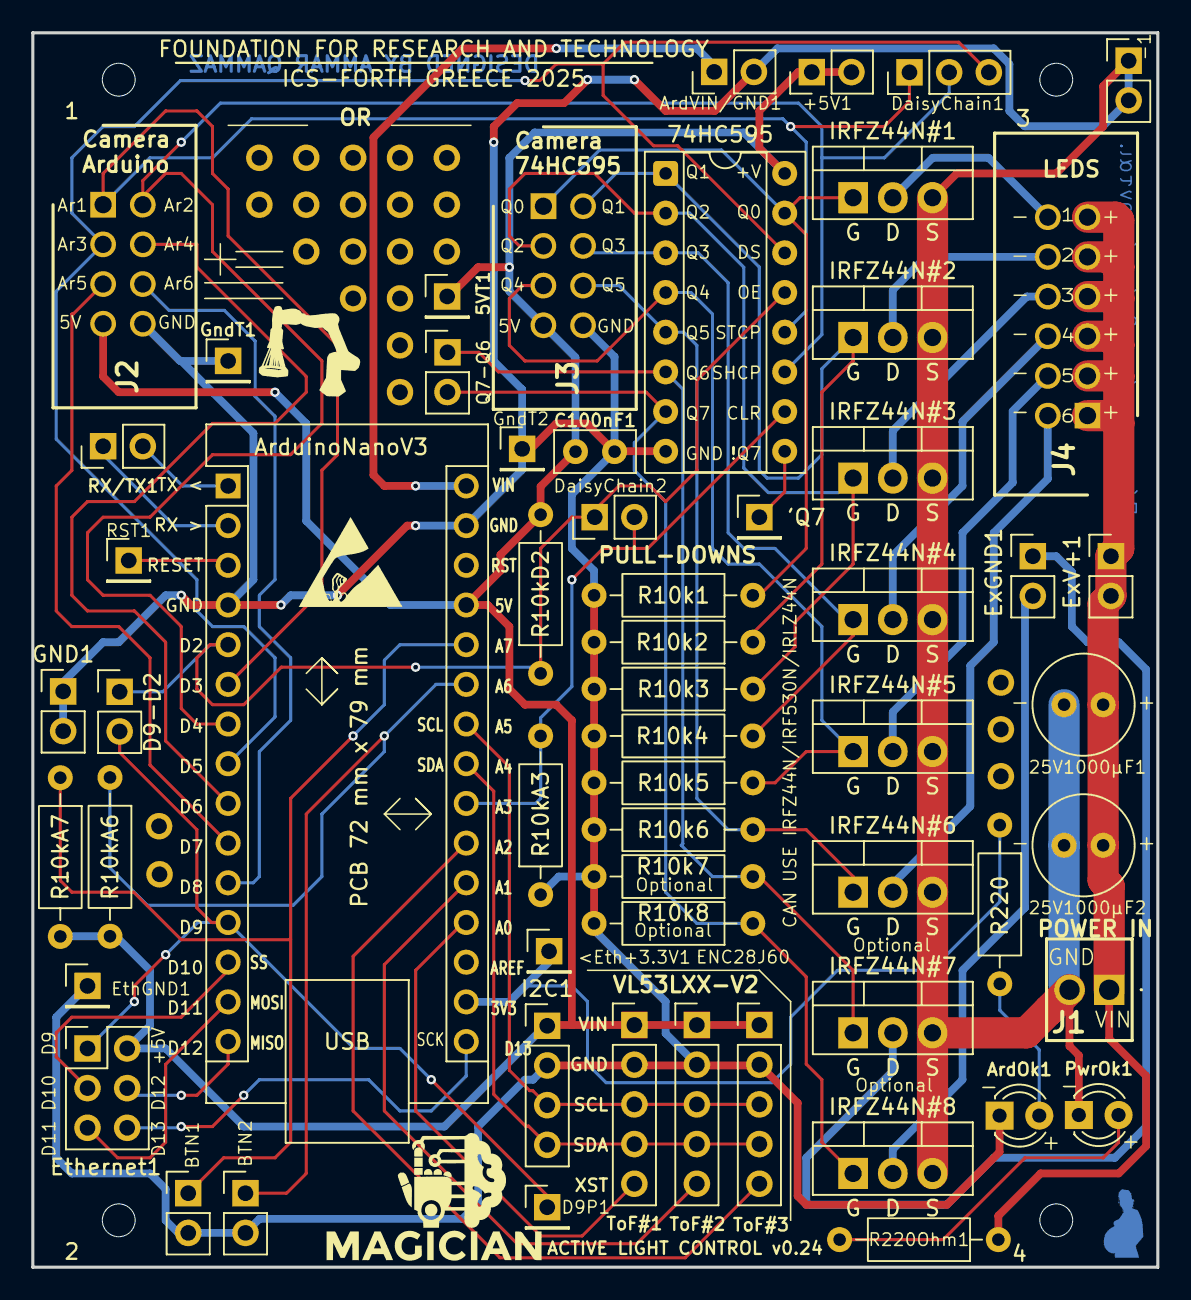
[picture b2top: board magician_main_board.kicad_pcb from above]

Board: 2 copper layers, 72.0 x 79.0 mm, 63 parts (0 on the bottom side), 47 nets.

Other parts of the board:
1, 2, 3, 4: MountingHole_2.1mm

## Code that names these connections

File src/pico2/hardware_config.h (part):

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//        * RP2350 Hardware Timer Alarms for exposure pulse safety guardrails.
//        * Fast-mode Plus I2C bus master (1 MHz) for MCP23018 expander and
//          three VL53L5CX Time-of-Flight ranging sensors.
//        * Push-button debounce state machine (PB0, PB1).
//    - Application & Transport Core (Core 1):
//        * Serial CDC (115200 baud) and W5500 SPI0 Ethernet transports.
//        * Multi-sensor ToF spatial analysis (center 4-zone matrix average).
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#define SDA_PIN                           4    // GP4: I2C Serial Data
#define SCL_PIN                           5    // GP5: I2C Serial Clock
#define MCP23018_ADDR                     0x20 // 7-bit I2C address (HW address --> A2=A1=A0=GND)
#define MCP23018_RESET_PIN                3    // GP3 : MCP23018 HW reset pin
#define MCP23018_INTA_PIN                 20   // GP28: Port A interrupt
#define MCP23018_INTB_PIN                 21   // GP21: Port B interrupt

// MCP23018 Registers (IOCON.BANK = 0 paired sequential memory map)
#define MCP23018_IODIRA                   0x00 // Port A Direction (1=Input, 0=Output)
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#define LIGHT_SCHEDULE_MAX_LENGTH         60    // 'S<digits>' maximum number of schedule entries
#define COMMAND_LINE_MAX_LENGTH           72    // Longest multi-character command line ('E','N','S','P')
// Power rails (Cam5 / v4 schematics):
//   +11.5VCC -> J16 "Cam. Pwr" jumper -> CAM_PWR -> camera connector J8 pin 4 (Sony XCG-CP510), panel I/O J13
//   +5VCC    -> Q19 P-FET -> Pico 2 VSYS whenever USB VBUS is absent (powers the Pico, and through its
//               3V3 regulator the MCP23018, ToF sensors and WIZ850io), panel I/O J13
// Switching +5VCC off without USB therefore cuts the board's own supply: refused unless VBUS is present.
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
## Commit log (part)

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2025-08-28 Add Arduino Nano Source code (0.26)
2025-08-28 add Kicad 9.0 PCB blueprint
2025-08-28 improve README
2025-08-28 add a photo
2025-08-28 add board
2025-08-29 add connectors
2025-09-24 added step file for main board
2026-05-15 add new Pico2/Multizone ToF sketch
2026-06-15 emmit all 64 distance values..
2026-06-15 bump 8x8 speed and deduplicate transmissions..
2026-06-16 make ethernet of board compatible with ethernet of camera..
